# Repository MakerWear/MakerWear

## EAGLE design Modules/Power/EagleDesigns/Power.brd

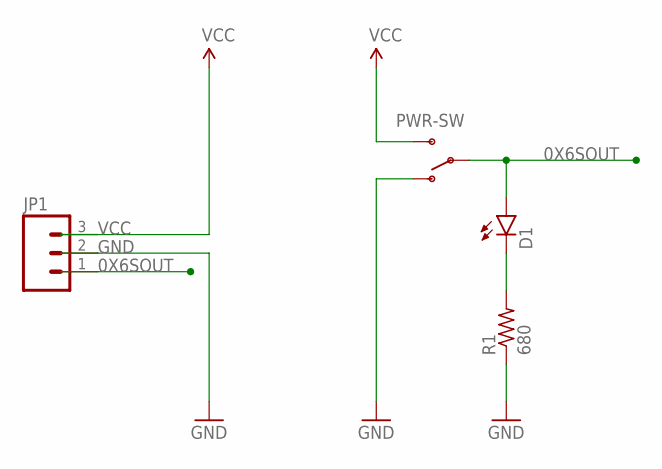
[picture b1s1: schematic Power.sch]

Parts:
D1: LED3MM
JP1: M03PTH; 1X03
PWR-SW: SWITCH-SPDTPTH; SWITCH-SPDT
R1: 680; R0603

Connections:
0X6SOUT: D1.A, JP1.1, PWR-SW.2
CUR-LIMIT-LED: D1.K (C), R1.2
GND: JP1.2, PWR-SW.1 (O), R1.1
VCC: JP1.3, PWR-SW.3 (S)

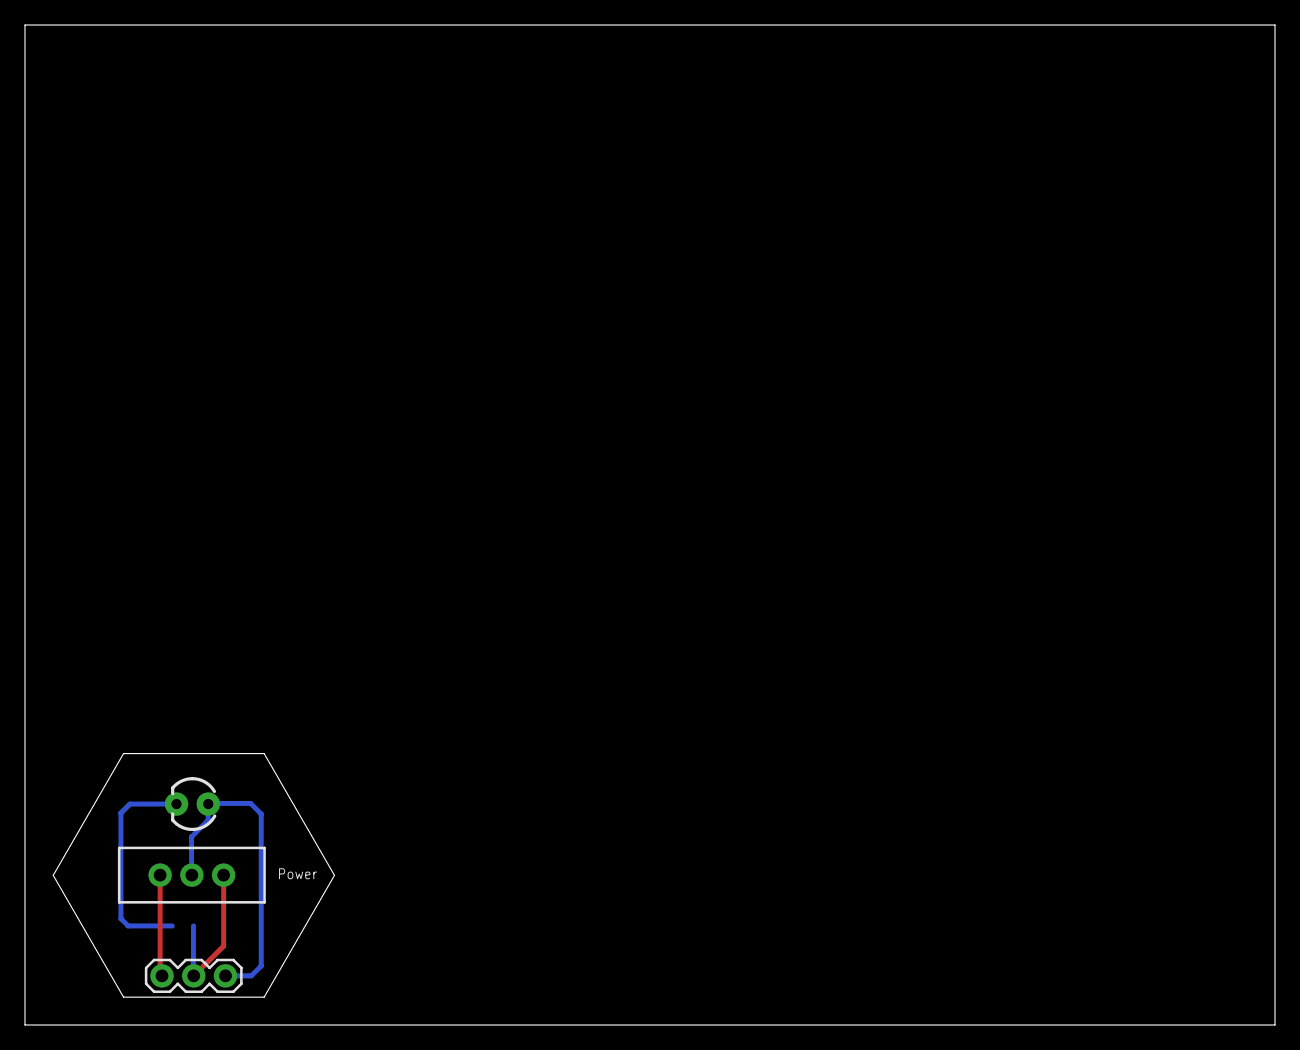
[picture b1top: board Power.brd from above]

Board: 2 copper layers, 100.0 x 80.0 mm, 4 parts (1 on the bottom side), 4 nets.

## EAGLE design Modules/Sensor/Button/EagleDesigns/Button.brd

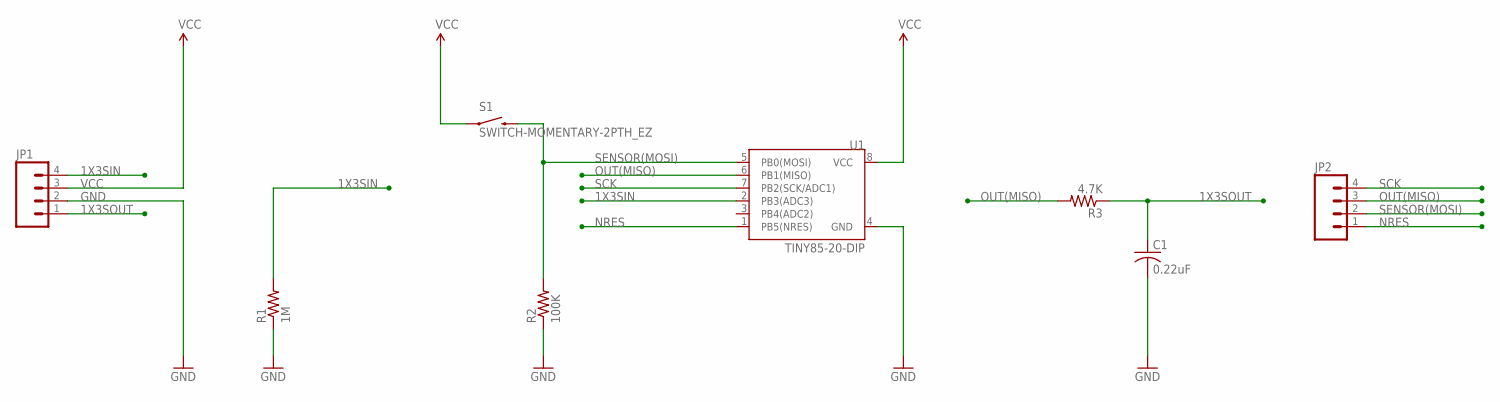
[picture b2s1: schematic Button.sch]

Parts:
C1: 0.22uF; C0402
JP1, JP2: M04PTH; 1X04
R1: 1M; R0603
R2: 100K; R0603
R3: 4.7K; R0603
S1: SWITCH-MOMENTARY-2PTH_EZ; TACTILE-PTH-EZ
U1: TINY85-20-DIP; DIP08

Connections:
1X3SIN: JP1.4, R1.2, U1.2 (PB3(ADC3))
1X3SOUT: C1.1, JP1.1, R3.1
GND: C1.2, JP1.2, R1.1, R2.1, U1.4 (GND)
NRES: JP2.1, U1.1 (PB5(NRES))
OUT(MISO): JP2.3, R3.2, U1.6 (PB1(MISO))
SCK: JP2.4, U1.7 (PB2(SCK/ADC1))
SENSOR(MOSI): JP2.2, R2.2, S1.3 (2), U1.5 (PB0(MOSI))
VCC: JP1.3, S1.1, U1.8 (VCC)

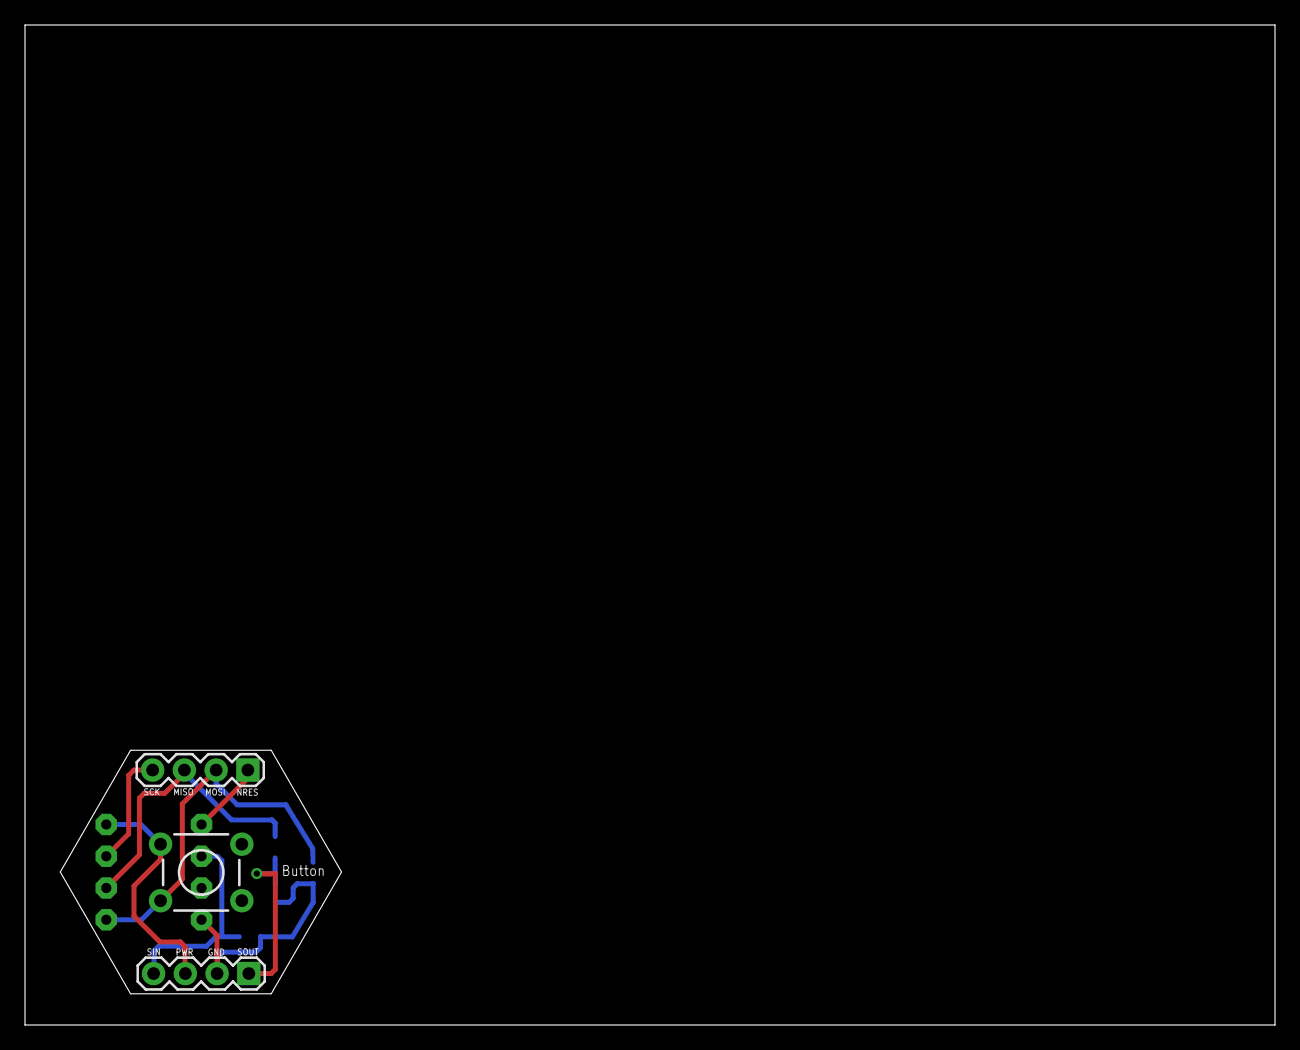
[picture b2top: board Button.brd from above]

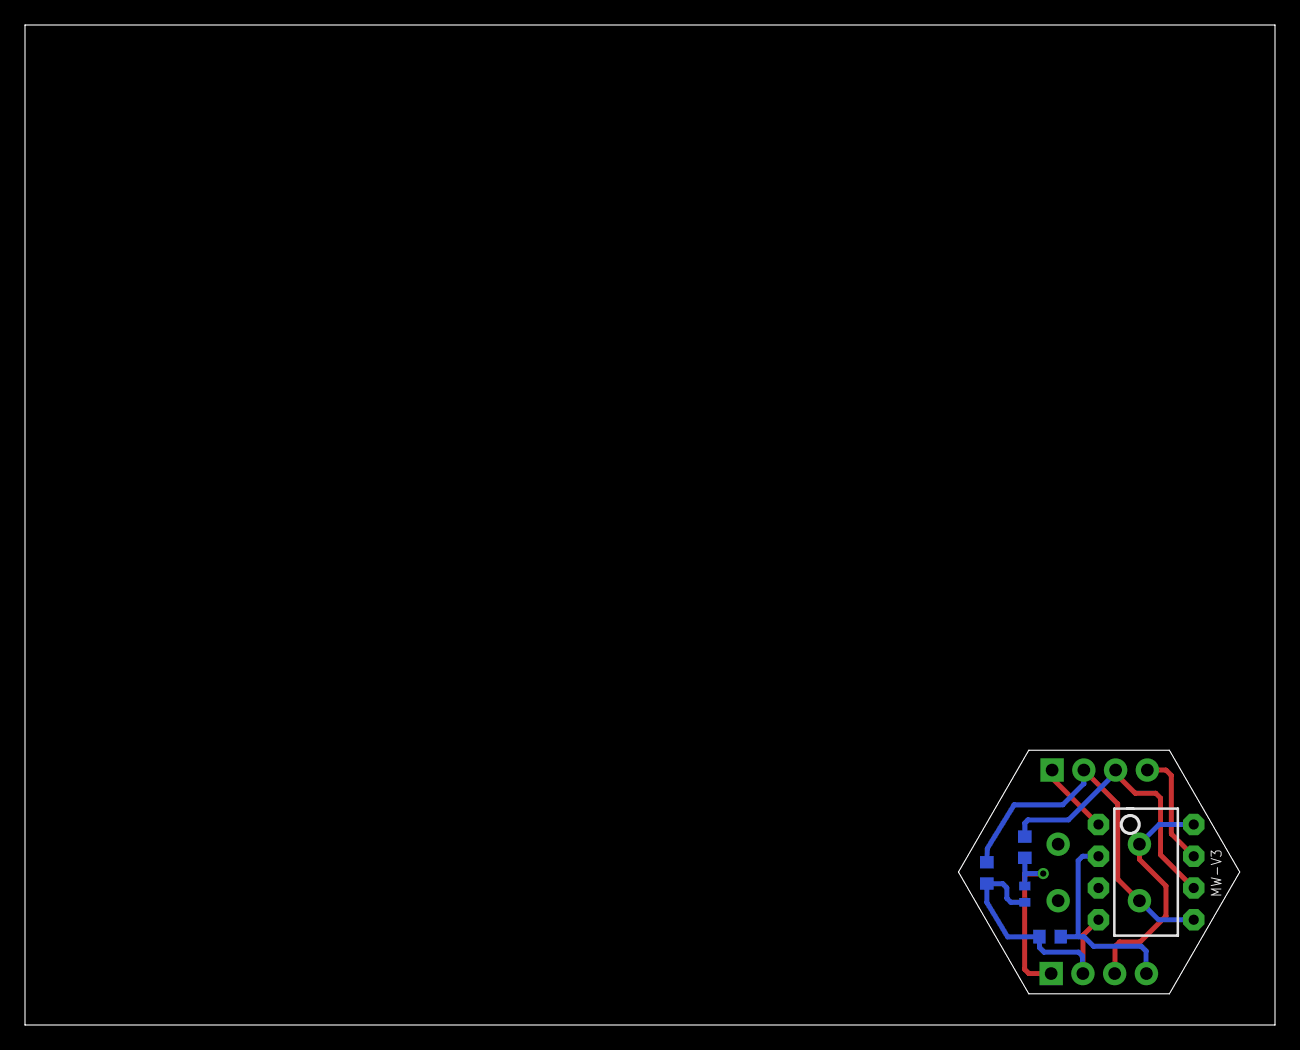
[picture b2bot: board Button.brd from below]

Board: 2 copper layers, 100.0 x 80.0 mm, 8 parts (5 on the bottom side), 8 nets.

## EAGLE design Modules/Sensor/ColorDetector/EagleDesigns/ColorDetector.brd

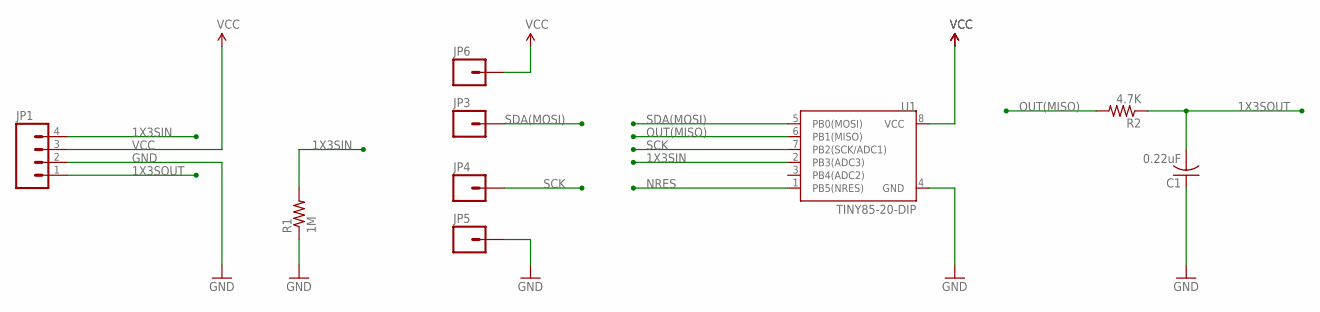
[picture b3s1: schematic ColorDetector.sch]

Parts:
C1: 0.22uF; C0402
JP1: M04PTH; 1X04
JP3, JP4, JP5, JP6: M01PTH; 1X01
R1: 1M; R0603
R2: 4.7K; R0603
U1: TINY85-20-DIP; DIP08

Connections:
1X3SIN: JP1.4, R1.2, U1.2 (PB3(ADC3))
1X3SOUT: C1.2, JP1.1, R2.1
GND: C1.1, JP1.2, JP5.1, R1.1, U1.4 (GND)
NRES: U1.1 (PB5(NRES))
OUT(MISO): R2.2, U1.6 (PB1(MISO))
SCK: JP4.1, U1.7 (PB2(SCK/ADC1))
SDA(MOSI): JP3.1, U1.5 (PB0(MOSI))
VCC: JP1.3, JP6.1, U1.8 (VCC)

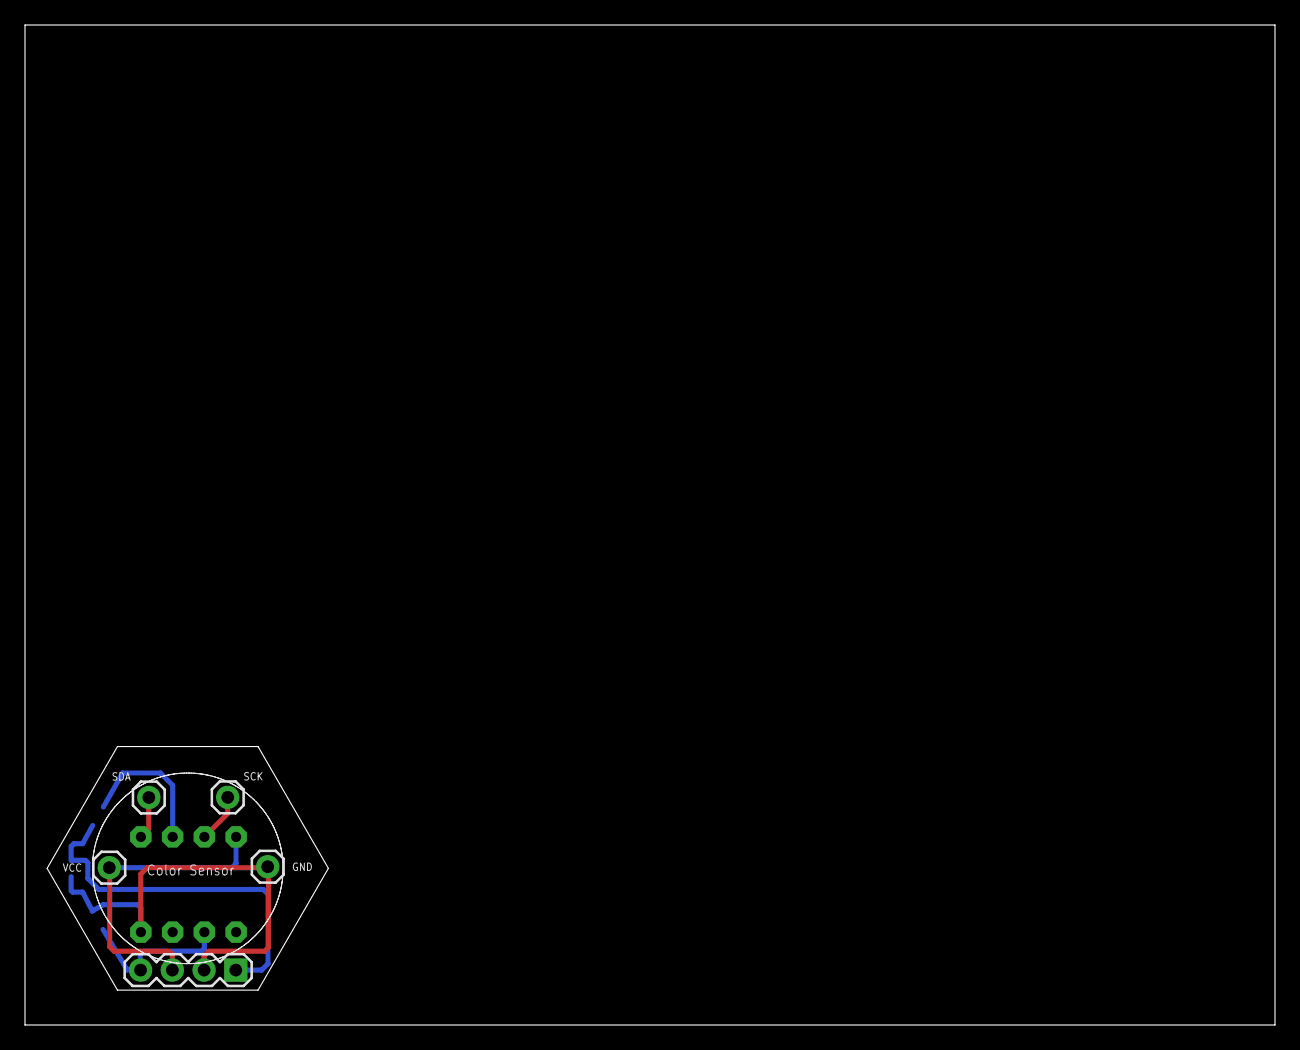
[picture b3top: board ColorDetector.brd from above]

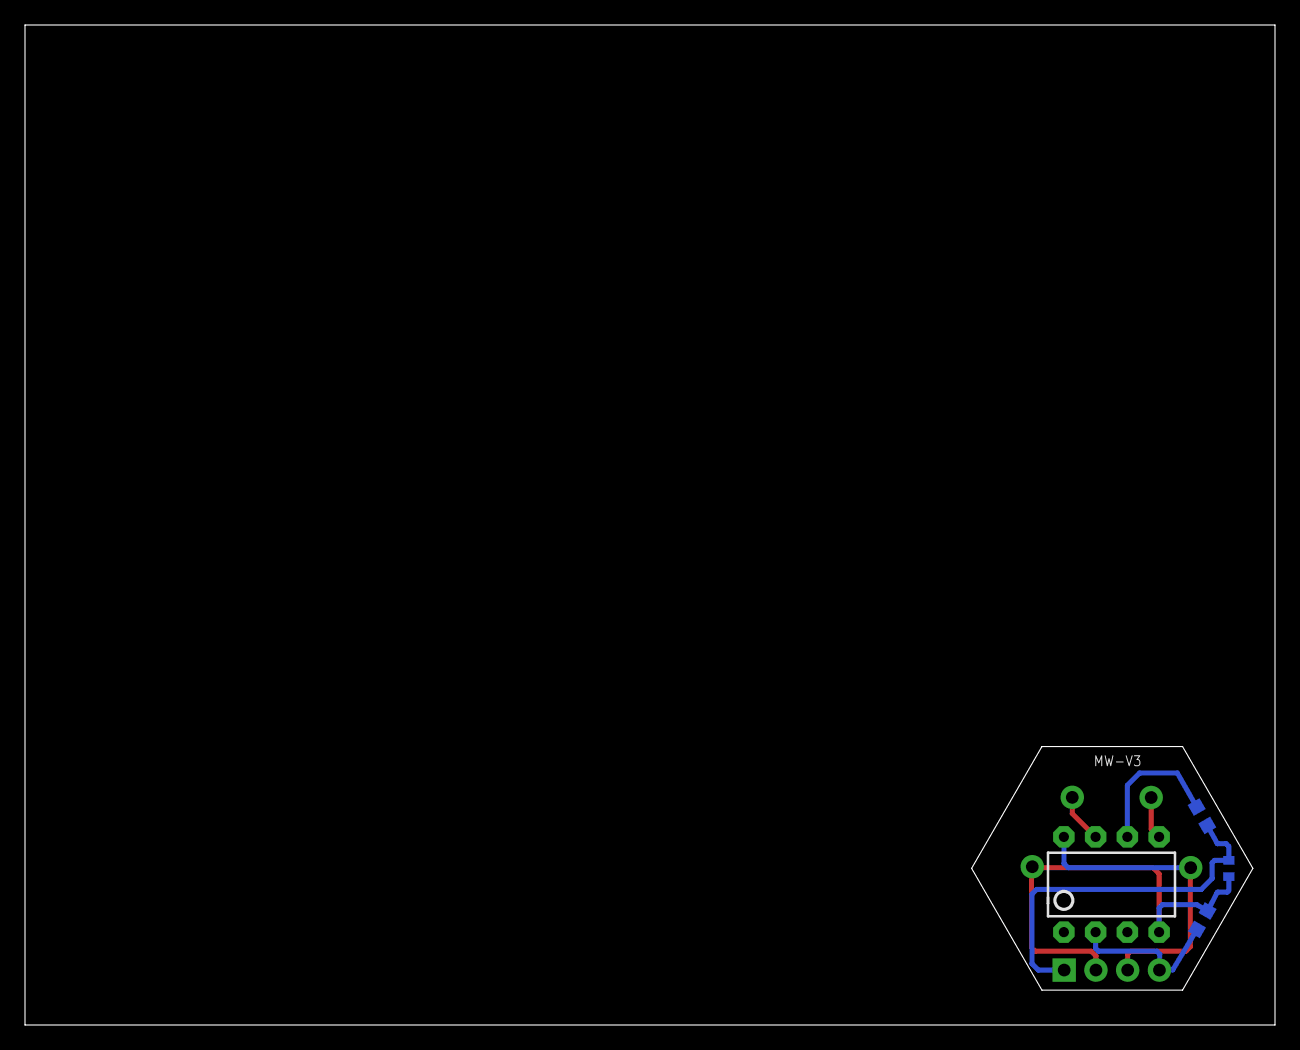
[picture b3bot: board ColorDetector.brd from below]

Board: 2 copper layers, 100.0 x 80.0 mm, 9 parts (4 on the bottom side), 7 nets.

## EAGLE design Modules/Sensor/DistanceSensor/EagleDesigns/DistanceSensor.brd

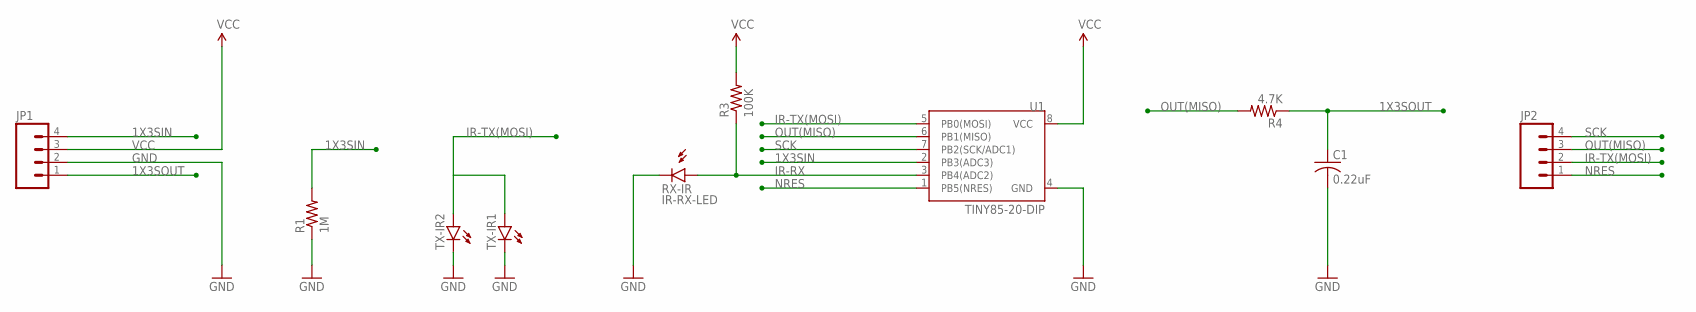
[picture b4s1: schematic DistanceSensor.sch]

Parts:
C1: 0.22uF; C0603
JP1, JP2: M04PTH; 1X04
R1: 1M; R0603
R3: 100K; R0603
R4: 4.7K; R0603
RX-IR: IR-RX-LED; LED5MM
TX-IR1, TX-IR2: LED5MM
U1: TINY85-20-DIP; DIP08

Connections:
1X3SIN: JP1.4, R1.2, U1.2 (PB3(ADC3))
1X3SOUT: C1.1, JP1.1, R4.1
GND: C1.2, JP1.2, R1.1, RX-IR.K (C), TX-IR1.K (C), TX-IR2.K (C), U1.4 (GND)
IR-RX: R3.1, RX-IR.A, U1.3 (PB4(ADC2))
IR-TX(MOSI): JP2.2, TX-IR1.A, TX-IR2.A, U1.5 (PB0(MOSI))
NRES: JP2.1, U1.1 (PB5(NRES))
OUT(MISO): JP2.3, R4.2, U1.6 (PB1(MISO))
SCK: JP2.4, U1.7 (PB2(SCK/ADC1))
VCC: JP1.3, R3.2, U1.8 (VCC)

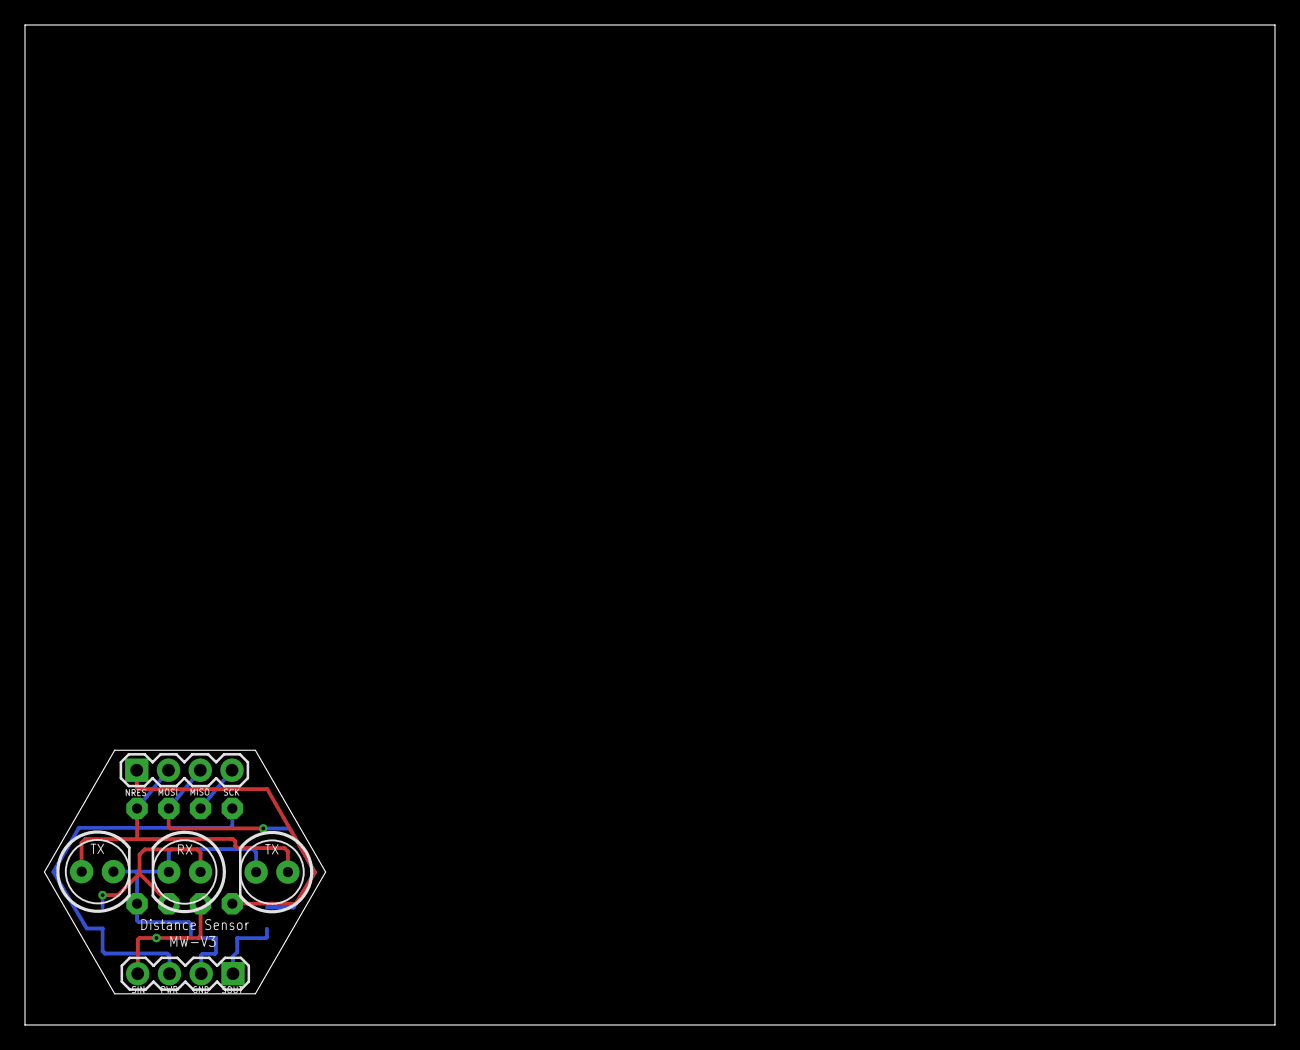
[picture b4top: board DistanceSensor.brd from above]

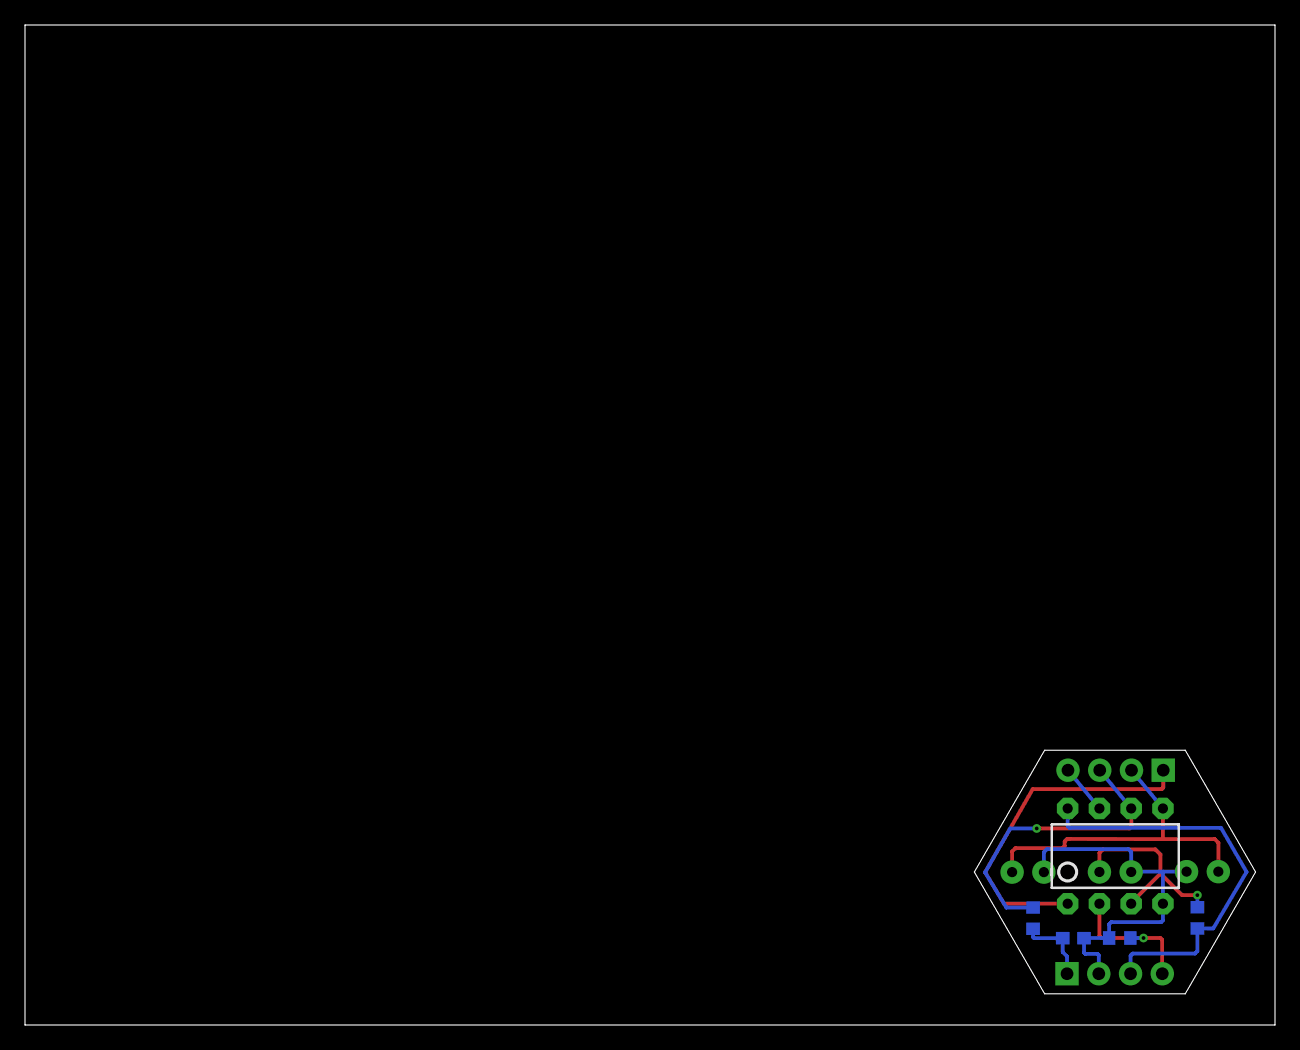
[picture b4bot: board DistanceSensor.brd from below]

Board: 2 copper layers, 100.0 x 80.0 mm, 10 parts (5 on the bottom side), 9 nets.

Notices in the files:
parts and their libraries:
SparkFun-LED: Licensing: Creative Commons ShareAlike 4.0 International - https://creativecommons.org/licenses/by-sa/4.0
